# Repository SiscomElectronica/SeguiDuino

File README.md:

# SeguiDuino

Shield seguidor de lineas para el Arduino UNO

## Descripcion

El proyecto consta de 3 archivos importantes:

*SiscomSeguidor_1.sch: Diagrama electrico del proyecto

*SiscomSeguidor_1.brd: Archivo del diseño del circuito impreso

*SiscomSeguidor_Componentes.pdf: Archivo PDF de los componentes del circuito

*SiscomSeguidor_Pistas.pdf: Archivo PDF con el diseño de pistas

## Consideraciones

Muchos componentes fueron modificados desde su libreria, asi que puede 
marcar algunos errores con respecto a su descarga y posterior modifcacion.

Con respecto a su fabricacion al no tener archivos (.gbr) gerber es 
necesario contactar al fabricante y proporcionarle el archivo 
Siscom_SEGUIDOR.brd para su posterior manufacturacion.

Diseñado por: [Josue Echeverria](https://www.facebook.com/josue.echeverria.583)

Team SISCOM.

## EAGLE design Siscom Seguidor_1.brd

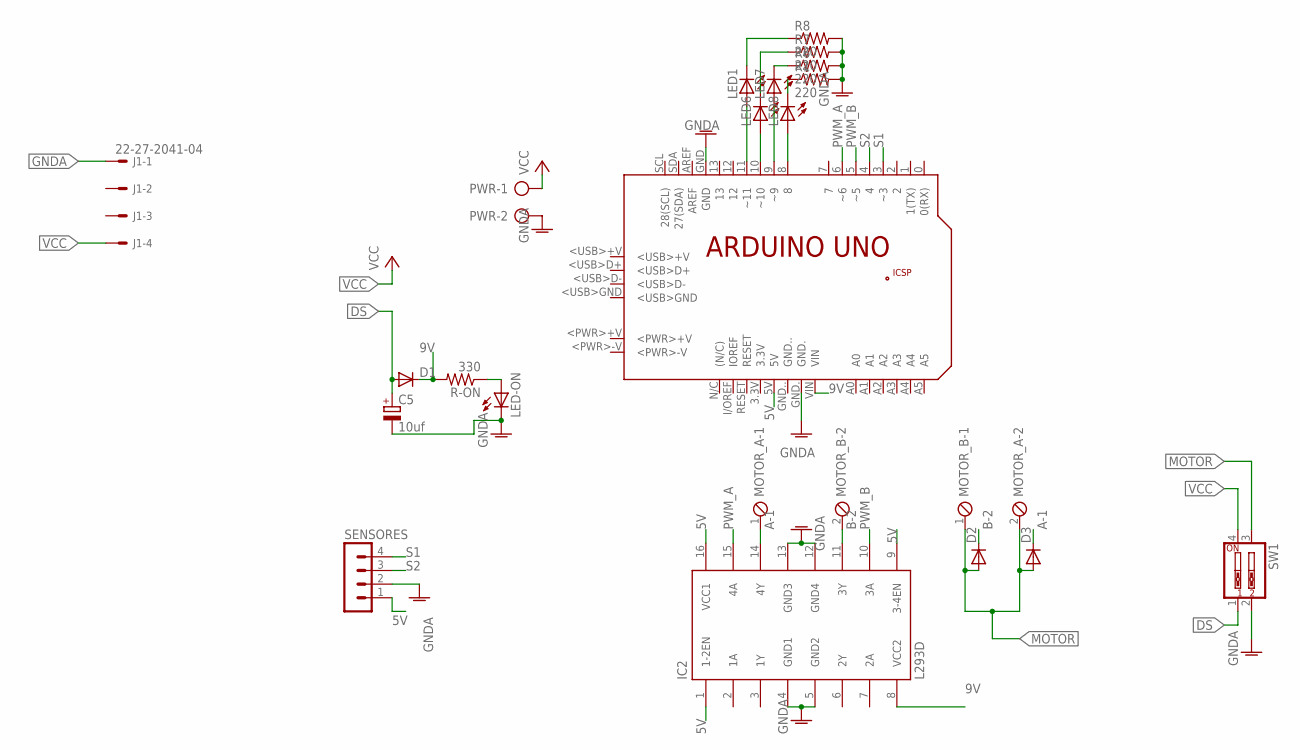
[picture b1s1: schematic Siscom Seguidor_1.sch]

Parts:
C5: 10uf; E2,5-6E
D1, D2, D3: 1N4148DO35-7; DO35-7
IC2: L293D; DIL16
J1: 22-27-2041-04; 6410-04
LED1, LED6, LED7, LED8: LED3MM
LED-ON: LED3MM
MOTOR_A: MPT2; 2POL254
MOTOR_B: MPT2; 2POL254
PCB2: ARDUINO_UNO
PWR: AK500/2
R1, R6, R7, R8: 220; 0204/7
R-ON: 330; 0204/7
SENSORES: MA04-1
SW1: SW_DIP-2; EDG-02

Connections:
5V: IC2.1 (1-2EN), IC2.9 (3-4EN), IC2.16 (VCC1), PCB2.5V, SENSORES.1
9V: D1.C, IC2.8 (VCC2), PCB2.VIN, R-ON.2
A-1: D3.C, IC2.14 (4Y), MOTOR_A.1
B-2: D2.C, IC2.11 (3Y), MOTOR_B.2
DS: C5.+, D1.A, SW1.1
GNDA: C5.-, IC2.4 (GND1), IC2.5 (GND2), IC2.12 (GND4), IC2.13 (GND3), J1.1, LED-ON.K (C), PCB2.GND, PCB2.GND., PWR.2, R1.2, R6.2, R7.2, R8.2, SENSORES.2, SW1.2
MOTOR: D2.A, D3.A, MOTOR_A.2, MOTOR_B.1, SW1.3
unnamed: LED-ON.A, R-ON.1
unnamed: LED8.K (C), R1.1
unnamed: LED7.K (C), R6.1
unnamed: LED6.K (C), R7.1
unnamed: LED1.K (C), R8.1
unnamed: LED7.A, PCB2.9 (~9)
unnamed: LED1.A, PCB2.11 (~11)
unnamed: LED6.A, PCB2.10 (~10)
unnamed: LED8.A, PCB2.8
PWM_A: IC2.15 (4A), PCB2.6 (~6)
PWM_B: IC2.10 (3A), PCB2.5 (~5)
S1: PCB2.3 (~3), SENSORES.4
S2: PCB2.4, SENSORES.3
VCC: J1.4, PWR.1, SW1.4

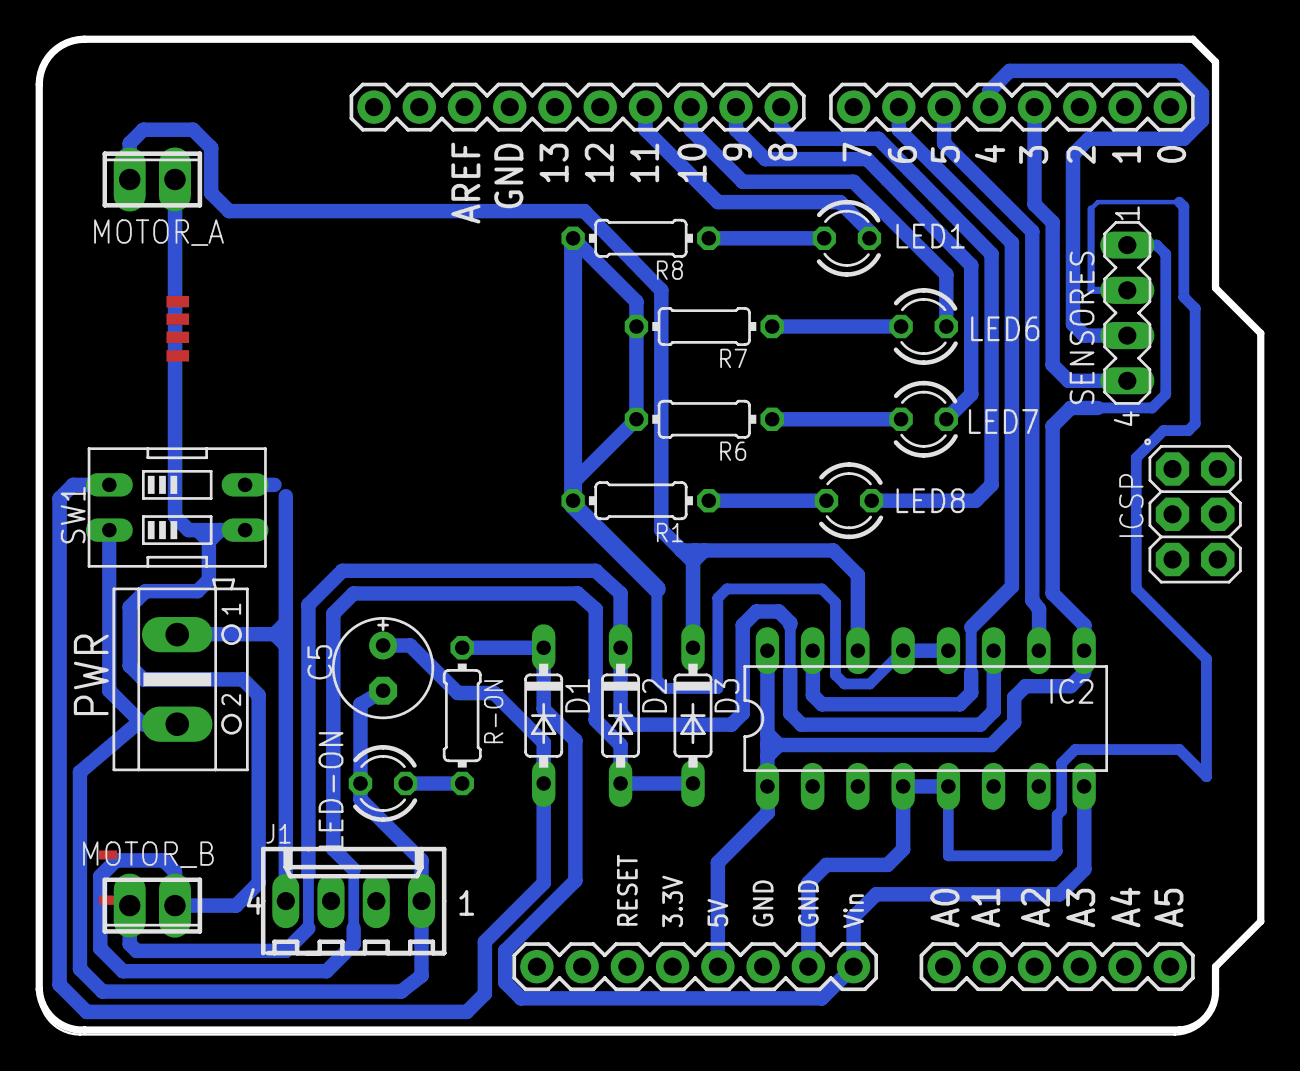
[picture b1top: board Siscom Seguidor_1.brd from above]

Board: 2 copper layers, 68.6 x 55.7 mm, 22 parts (0 on the bottom side), 21 nets.

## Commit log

2017-08-21 Primer commit
2017-08-21 Modificacion README.md
2017-08-21 PDF a imprimir
2017-08-21 Detalles
